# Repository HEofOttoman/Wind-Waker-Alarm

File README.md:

# Wind Waker Alarm
<!--  -->

A waker/alarm to wake me up that also can act as a macropad, including a rechargable battery and wireless capabilities.

This repository contains folders for the following:
- Schematics: Designs for the wiring (pcb?)
- Case: CAD models of the alarm
- Firmware: Firmware for the alarm clock

### Future Plans for a V2

- Reading music from USB
- Speaker/audio module to play the music
- Time from a real RTC
- Radio receiver

## Gallery

## BOM (TBC)
| Qty | Part Name                    | Source                                                                                                                                                                                                                                              | Price (AUD) |
|-----|------------------------------|-----------------------------------------------------------------------------------------------------------------------------------------------------------------------------------------------------------------------------------------------------|-------------|
| 1   | Lolin C3-Mini ESP32          | Provided in Kit                                                                                                                                                                                                                                     | -           |
| 1   | 2.5in TFT Display            | Provided in Kit                                                                                                                                                                                                                                     | -           |
| 12  | MX Switches                  | Provided in Kit                                                                                                                                                                                                                                     | -           |
| 1   | 3.3v Piezo Buzzer            | Provided in Kit                                                                                                                                                                                                                                     | -           |
| -   | Jumper cables                | Provided in Kit                                                                                                                                                                                                                                     | -           |
| 1   | WEMOS D1 Mini Battery Shield | [Aliexpress?](https://www.aliexpress.com/item/1005010742110580.html)                                                                                                                                                                                | $1.44       |
| 16  | Stackable Header Pins        | [core electronics](https://core-electronics.com.au/header-stackable-01x20-254mm-tht.html)                                                                                                                                                           | $0.90       |
| 1   | 3.7v LiPo Battery            | [Temu (polarity with shield check needed)](https://www.temu.com/au/302025-3-7v-150mah-lithium-polymer-battery-with-built-in-multi-protection-circuitry-a-compact-rechargeable-lithium-polymer-battery-suitable-for-dashcams-g-606328114217288.html) | $2.85       |
| 1   | Custom PCB                   | JLCPCB                                                                                                                                                                                                                                              | ~$5         |

*Made with [Markdown tablesgenerator.com](https://www.tablesgenerator.com/markdown_tables)*

<!-- - 1x Lolin C3 Mini ESP 32
- 1x 2.25in TFT display
- 12x Keyboard Switches
- 1x 3.3V Piezo Buzzer
- Some Jumper Cables for wiring
- 1x WEMOS D1 Mini Battery Shield
- 16x Stackable header pins
- 1x 3.7v LiPo battery (check the polarity of the shield)
- PCB 93.620mm x 51.380mm
    - 4.380 -->

## References
- [Guide](https://blare.hackclub.com)!
- Several google searches
- Battery shield [docs?](https://www.wemos.cc/en/latest/d1_mini_shield/battery.html)

*Made for [blare](https://blare.hackclub.com)!*

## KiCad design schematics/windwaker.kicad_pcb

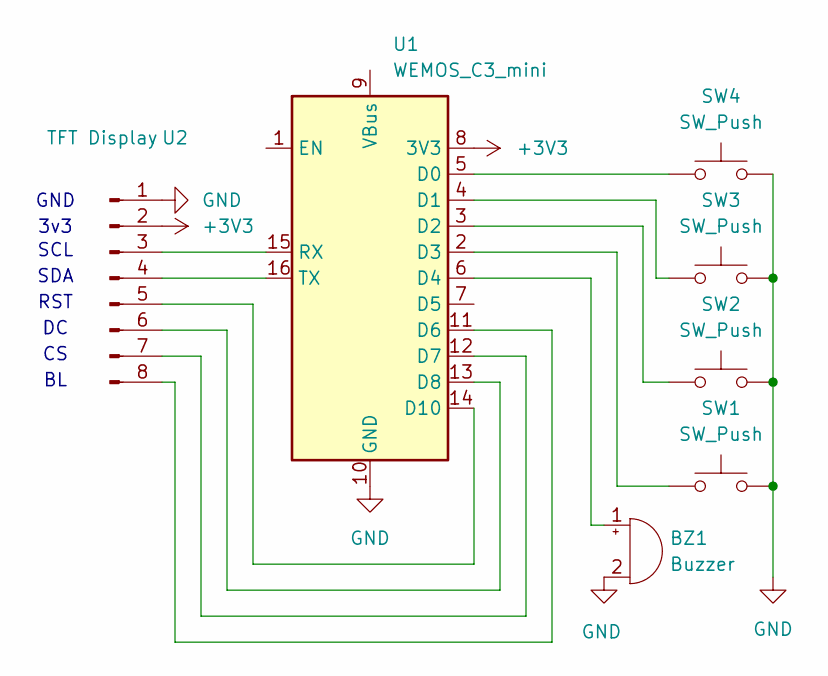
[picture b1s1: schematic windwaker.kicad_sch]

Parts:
BZ1: Buzzer; Buzzer_12x9.5RM7.6
SW1, SW2, SW3, SW4: SW_Push; SW_Cherry_MX_1.00u_PCB
U1: WEMOS_C3_mini
U2: TFT Display; TFT-Display_ST7789_2.25in_76x284_8P

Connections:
+3V3: U1.8 (3V3), U2.2
GND: BZ1.2 (-), SW1.2, SW2.2, SW3.2, SW4.2, U1.10 (GND), U2.1
unnamed: BZ1.1 (+), U1.6 (D4)
unnamed: SW4.1, U1.5 (D0)
unnamed: SW3.1, U1.4 (D1)
unnamed: SW2.1, U1.3 (D2)
unnamed: SW1.1, U1.2 (D3)
unnamed: U1.11 (D6), U2.8
unnamed: U1.12 (D7), U2.7
unnamed: U1.13 (D8), U2.6
unnamed: U1.14 (D10), U2.5
unnamed: U1.15 (RX), U2.3
unnamed: U1.16 (TX), U2.4

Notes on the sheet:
SCL
3v3
GND
SDA
RST

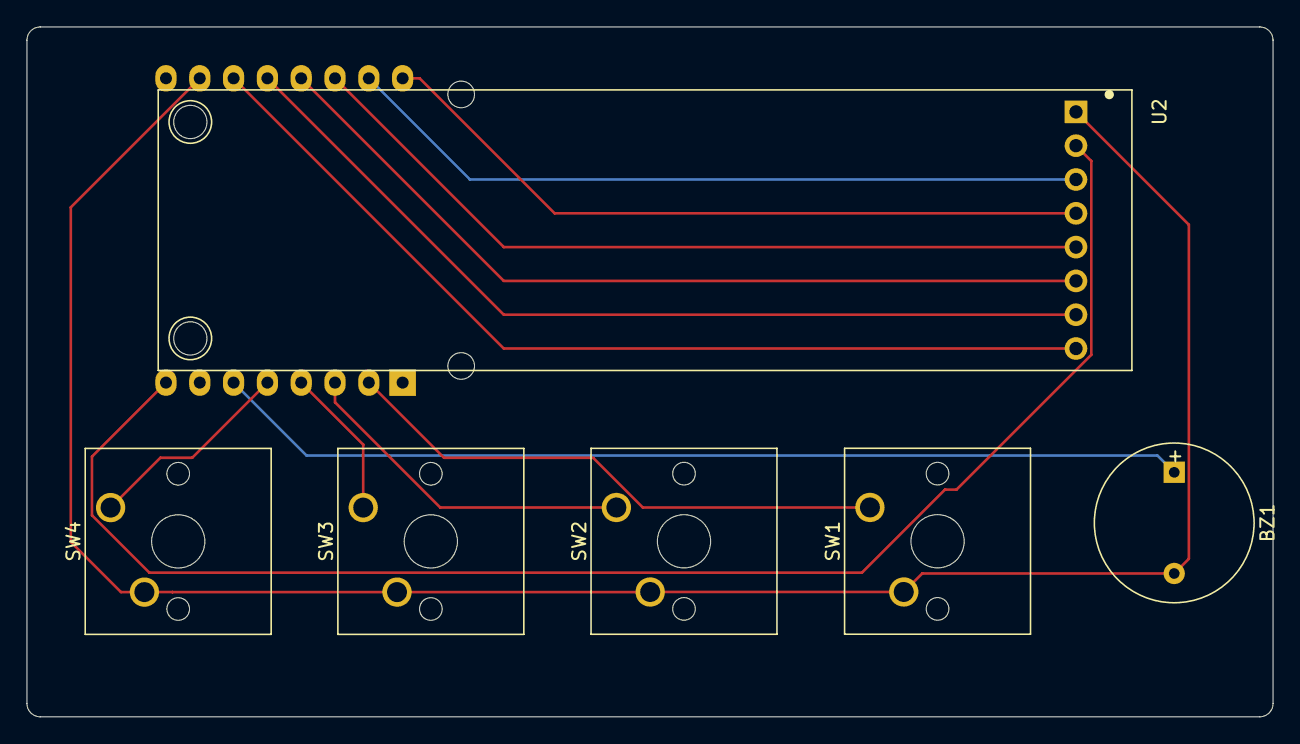
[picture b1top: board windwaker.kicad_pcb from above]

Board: 2 copper layers, 93.6 x 51.8 mm, 7 parts (1 on the bottom side), 13 nets.

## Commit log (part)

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2026-06-30 started writing firmware
    🙏🙏🙏🙏 readme too
2026-06-30 more schematics
    schematic attempt
    readme updates
